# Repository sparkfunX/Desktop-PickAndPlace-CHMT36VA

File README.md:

SparkFun Charm High Desktop Pick and Place
========================================

The CHMT36VA is a $2800 desktop sized pick and place machine from Charm High. We use it to produce a variety of designs, 50 to 100pcs at a shot. It works very well for low-volume high-mix pick and place of 0603 based designs.

The main purposed of this repo is the [Eagle Conversion ULP](https://github.com/sparkfunX/Desktop-PickAndPlace-CHMT36VA/tree/master/Eagle-Conversion) and the English Language file. The Conversion ULP offers the user a GUI that looks like this:

This allows the user to take in an Eagle BRD file and output the recipe file that the CHMT36VA expects. This cuts down on setup time of the machine dramatically.

The [English Language conversion file](https://github.com/sparkfunX/Desktop-PickAndPlace-CHMT36VA/tree/master/Language-File) is our translation and typo fixes of the Charm High provided english file.

Do you have one of these machines? Want to share your tips and tricks and ask other owners a question? Join the [Desktop Pick and Place google group](https://groups.google.com/d/forum/desktop-pick-and-place)!

Be sure to checkout our posts on the machine:

* [Unboxing](https://www.sparkfun.com/sparkx/blog/2586)
* [Leader Cheaters](https://www.sparkfun.com/sparkx/blog/2588)
* [Installing the Charm High Software](https://www.sparkfun.com/sparkx/blog/2594)
* [A better English translation](https://www.sparkfun.com/sparkx/blog/2595)
* [An EAGLE ULP](https://www.sparkfun.com/sparkx/blog/2591) to setup new jobs on the machine quickly

Repository Contents
-------------------

* **/Eagle-Conversion** - Takes an EAGLE design and outputs a work file complete with feeder data. See [SparkFun Charm EAGLE Conversion ULP](https://www.sparkfun.com/sparkx/blog/2591) for more information.
* **/KiCad-Conversion** - Same as EAGLE but less developed. It works, but less bells and whistles.
* **/Language-File** - A new smt_English.qm file for easier to understand error messages and buttons
* **/Software** - The various versions of the Windows based Charm High software
* **/User-Manuals** - Various manuals from different machines in an attempt to piece together various poorly translated or documented features

Related Projects
----------------

* [PNPConvert](https://github.com/hydra/pnpconvert) Conversion utility with DipTrace support, written in Groovy.

License Information
-------------------

This product is _**open source**_! 

Please review the LICENSE.md file for license information. 

If you have any questions or concerns on licensing, please contact techsupport@sparkfun.com.

Please use, reuse, and modify these files as you see fit. Please maintain attribution to SparkFun Electronics and release any derivative under the same license.

Distributed as-is; no warranty is given.

- Your friends at SparkFun.

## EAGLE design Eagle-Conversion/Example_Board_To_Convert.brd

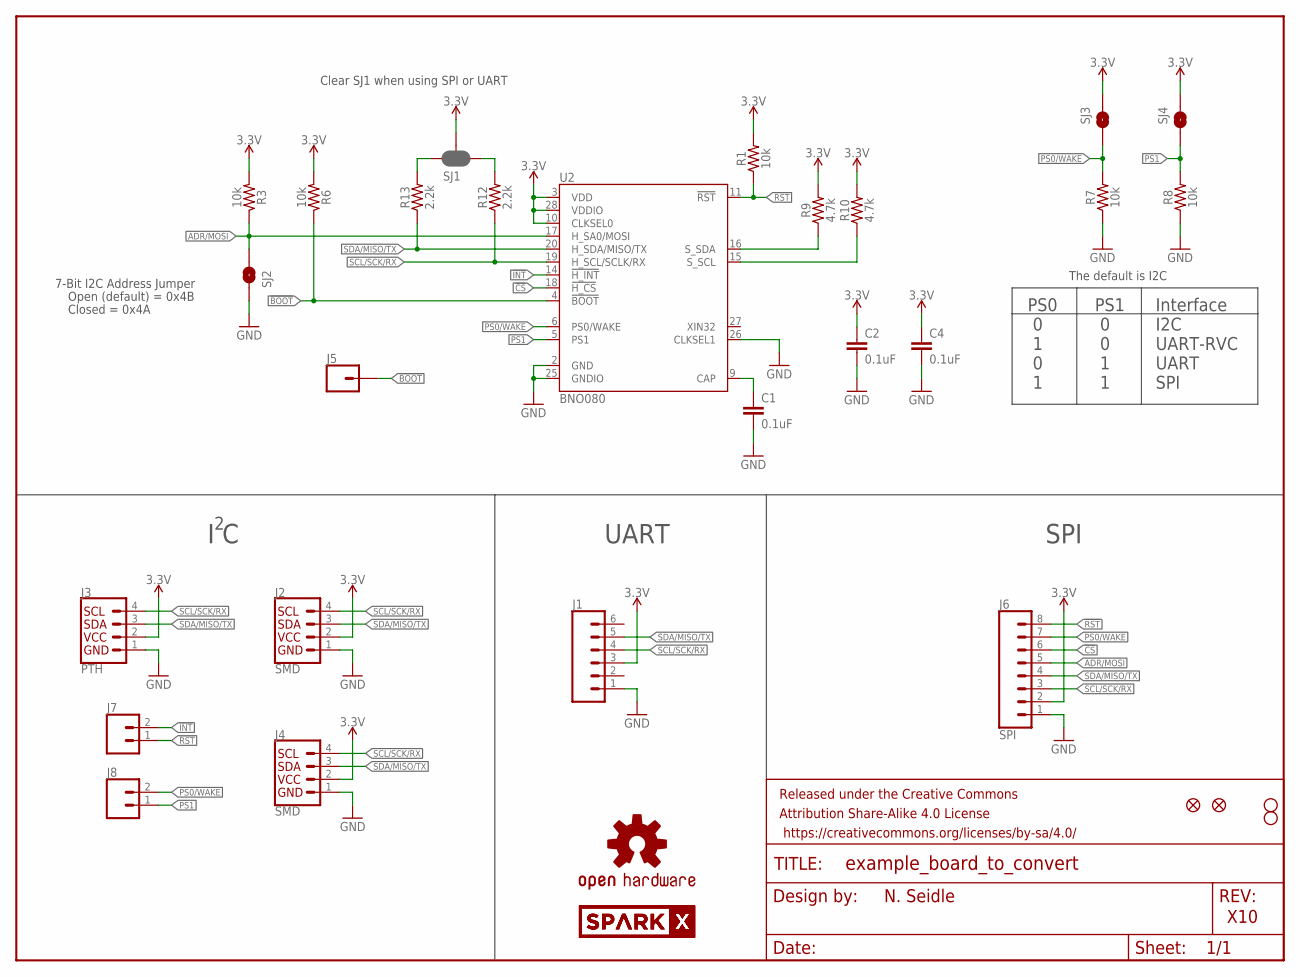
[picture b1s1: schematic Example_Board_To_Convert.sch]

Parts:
C1, C2, C4: 0.1uF; 0603
FRAME1: FRAME-LETTER; CREATIVE_COMMONS
J1: CONN_06NO_SILK_FEMALE_PTH; 1X06_NO_SILK
J2, J4: SMD; 1X04_1MM_RA
J3: PTH; 1X04_NO_SILK
J5: CONN_01PTH_NO_SILK_YES_STOP; 1X01_NO_SILK
J6: SPI; 1X08_NO_SILK
J7, J8: CONN_021X02_NO_SILK; 1X02_NO_SILK
JP2, JP6: FIDUCIALUFIDUCIAL; MICRO-FIDUCIAL
JP3, JP4: STAND-OFF
LOGO1: OSHW-LOGOMINI; OSHW-LOGO-MINI
R1, R3, R6, R7, R8: 10k; 0603
R9, R10: 4.7k; 0603
R12, R13: 2.2k; 0603
SJ1: JUMPER-SMT_3_2-NC_PASTE_SILK; SMT-JUMPER_3_2-NC_PASTE_SILK
SJ2, SJ3, SJ4: SOLDERJUMPERNO; SJ_2S-NO
U2: BNO080; LGA-28
U$1, U$2: SPARKX-LOGO3; SPARKX-SMALL

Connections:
3.3V: C2.1, C4.1, J1.3, J2.2 (VCC), J3.2 (VCC), J4.2 (VCC), J6.2, R1.2, R3.2, R6.2, R9.2, R10.2, SJ1.2, SJ3.1, SJ4.1, U2.3 (VDD), U2.10 (CLKSEL0), U2.28 (VDDIO)
!BOOT: J5.1, R6.1, U2.4 (!BOOT)
!CS: J6.6, U2.18 (!H_CS)
!INT: J7.2, U2.14 (!H_INT)
!RST: J6.8, J7.1, R1.1, U2.11 (!RST)
ADR/MOSI: J6.5, R3.1, SJ2.2, U2.17 (H_SA0/MOSI)
CAP: C1.1, U2.9 (CAP)
GND: C1.2, C2.2, C4.2, J1.1, J2.1 (GND), J3.1 (GND), J4.1 (GND), J6.1, R7.1, R8.1, SJ2.1, U2.2 (GND), U2.25 (GNDIO), U2.26 (CLKSEL1)
PS0/WAKE: J6.7, J8.2, R7.2, SJ3.2, U2.6 (PS0/WAKE)
PS1: J8.1, R8.2, SJ4.2, U2.5 (PS1)
SCL/SCK/RX: J1.4, J2.4 (SCL), J3.4 (SCL), J4.4 (SCL), J6.3, R12.1, U2.19 (H_SCL/SCLK/RX)
SCL_PU: R12.2, SJ1.1
SDA/MISO/TX: J1.5, J2.3 (SDA), J3.3 (SDA), J4.3 (SDA), J6.4, R13.1, U2.20 (H_SDA/MISO/TX)
SDA_PU: R13.2, SJ1.3
S_SCL: R10.1, U2.15 (S_SCL)
S_SDA: R9.1, U2.16 (S_SDA)

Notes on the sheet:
N. Seidle
X10
7-Bit I2C Address Jumper
Closed = 0x4A
Open (default) = 0x4B
PS0 0 1 0 1
PS1 0 0 1 1
Interface I2C UART-RVC UART SPI
The default is I2C
Clear SJ1 when using SPI or UART
I C
UART
SPI

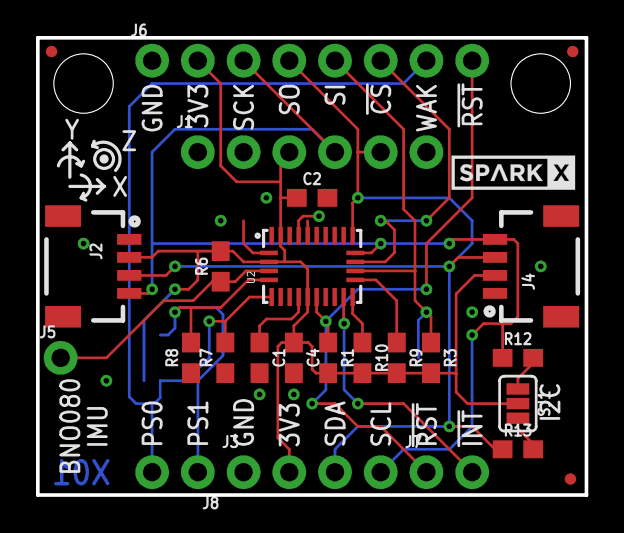
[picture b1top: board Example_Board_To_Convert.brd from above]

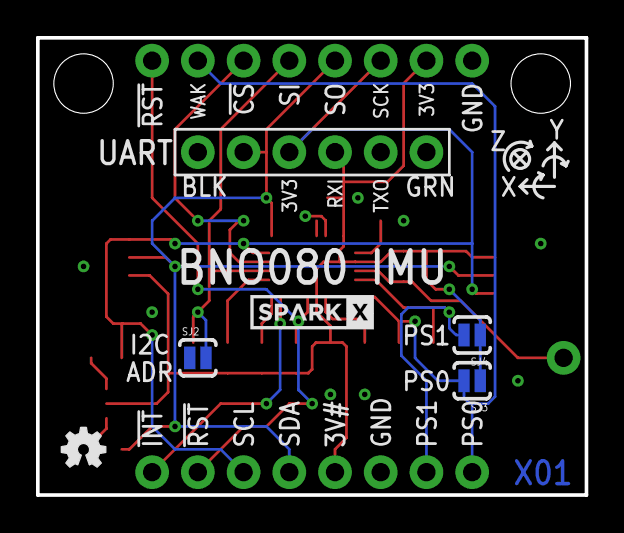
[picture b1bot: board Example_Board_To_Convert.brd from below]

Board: 2 copper layers, 30.5 x 25.4 mm, 34 parts (5 on the bottom side), 16 nets.

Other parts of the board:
JP1: FIDUCIALUFIDUCIAL; MICRO-FIDUCIAL

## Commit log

2018-01-25 Adding credentials shield
2018-01-25 Making credential search work
2018-01-26 Adding KiCad scripts and manuals
2018-01-29 Adding KiCad converter. Adding manuals.
2018-01-29 Adding Qt editor for Windows
2018-01-29 Readme update
2018-02-01 Correcting white space bug.
    If component was not found in feeder data the program would fail. Fix was to only check for component specific data if it was indeed located in the feeder data array.
2018-02-02 Adding readme for kicad gotchas to avoid.
2018-02-08 Work in progress
2018-02-09 Implemented two layer export capabilities and length/width of component
2018-02-09 Major restructuring of the ULP with several new features
    a) Added GUI to review Part Placement and Feeder configuration
    b) Allow usage of local and remote spreadsheet for feeders
    c) Added column autodetection for feeder configuration
    d) Added board statistics
    e) Added automatic offset correction
    -> Only positive coordinates will be in the final file
2018-02-09 Remove offset from KiCad converter
2018-02-09 Adding ignore for credentials
2018-02-09 Revert "Adding readme for kicad gotchas to avoid."
    This reverts commit 1ee665d34516afad8c6f67a0673c987d52c927f7.
2018-02-09 Fixing bad defaults
2018-02-09 Fix issue 6 - relative tape angles now being read
2018-02-09 Fixing issue 7 - centroids now calculated correctly
2018-02-09 Adding toLower() on part names for better matching
2018-02-09 Adding toLower for better feeder ID
2018-02-09 Fixed issue 2 - pulls in human readable comp names
2018-02-10 Fixed issue 3 - adding default file save location
2018-02-12 Several improvements concerning offset handling a) Added possibility to select between automatic and manual offset b) Added warning if negative coordinates are present d) Added preview of placement c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
2018-02-13 Fixed width/height for cameras to detect outlines correctly
2018-02-14 Allows to config trays (and pick-up pockets) to be configured with the ULP
2018-03-05 Offset option is now loaded from file
2018-03-06 Getting NoMount parts from spreadsheet to correctly read. Not yet working.
2018-03-06 getFeederID modified to find partial matches of component name and alias from sheet
2018-03-06 Updated translations for the inner systems menu.
2018-03-20 Fixing 'No Mount' checking from spreadsheet. Adding GUI image.
2018-03-20 Adding GUI image to readme.
2018-03-31 Adding google group to readme
2018-03-31 Adding catch for component angles that are too negative.
2018-03-31 Fix issue 16: Ignore blank lines in feeder spreadsheet.
2018-03-31 Fix issue #15. Tighten comparison of component names to feeder names and aliases. Fix double listings in "Feeders Used" tab.
2018-03-31 Comment and whitespace cleanup
2018-03-31 White space and comment changes
2018-04-08 Adding tips and tricks
2018-04-09 Add internal images, some random hints, updated ticks-n-tips readme
2018-06-25 Fixed some minor issues and added fiducial handling for better pcb calibration
2018-06-25 Fixed some bugs and added possibility to turn of fiducial referencing and added a third mark to Nathans PCB example
2018-07-26 Adding firmware from Rickard. Adds 3rd cal spot and some translation fixes.
2018-08-17 Adding manuals from jmartinis
2018-08-27 Adding editable versions of the improved user manuals and undocumented menus.
2018-10-11 Adding Turkish translation of CHM-T36VA user manual. Thanks Naci!
2018-10-21 Add PCB images
2018-11-21 Started work. In progress
2019-01-15 Adding hardware pinout, ic bom list, and mechanics specs.
2019-03-05 apply change from steve, 02-10-18: py3 mainly
2019-03-05 repr and component_name()
2019-03-05 Fixing awful loop iteration
2019-03-05 bad print messages
2019-03-05 Improve printing infos
2019-03-05 fix print message
2019-03-05 using the spreadsheet key at the begining of the file
2019-03-05 used in design become count in design
2019-03-05 fix for fiducial
2019-03-05 NewSkip cmp are added to the output file as notmounted, for manual add
2019-03-05 args, message and help
2019-03-08 Fix component rotation
2019-03-08 Apply global X/Y correction to NoMount and NewSkip components as well
2019-03-08 Add command line arguments for bottom pos files Rotation and x values have to be mirrored.
2019-03-08 Apply rotation correction to all components, including NoMount and NewSkip
2019-03-08 Keep component value/reference for NewSkip components
2019-04-03 Add link to PnPConvert.
2019-04-17 Support ods/fods/xls/xlsx feeder data files (uses pyexcel instead of builtin csv.reader)
2019-04-18 Set the default output file name using the comp. position file name
2019-04-18 DPV file : include only the filename, not the full path
2019-04-18 Match Eagle script capabilities and output syntax
2019-04-18 Do not include NoMount and add an option for NewSkip components. For NewSkip the feeder ID is set to 99 to avoid triggering an error in the CharmHigh software.
2019-04-18 Auto detect fiducials based on designator
2019-04-18 Add a command line option for a global offset
2019-04-18 KiCad conversion script documentation
2019-04-18 KiCad conversion README typos and clarification
2019-04-29 Compatibility for older py versions
2019-06-09 Add BOM Generator, with automount entry
2019-06-12 Update ConvertToCharm.ulp
    Changed FEEDER_NO_MOUNT from 30 to 999 for requested PR.
2019-06-27 removing unused Reel file
2019-06-27 adding first version, never used in prod
2019-06-27 adding doc
2019-07-11 KiCad conversion: Fix crash when a cut tape row has no alias
2019-07-11 KiCad conversion: strip whitespace from text based columns
2019-10-01 avoid strip on None value
2019-10-01 added Panel settings
2019-10-02 added Panel settings dialogue and explanatory image
2019-10-02 dose no longer ignore Stop-Marks within documents
2019-10-02 is now executable in schematic
2019-10-03 recognises double-sided parts now mostly useful for Fiducials
2019-10-04 dose accept the normal google spreadsheet url now not just the download url
2019-10-15 bug fixes: does no longer have huge coordinates
2019-10-16 Fixed panel offset caluclation and handling to produce correct results
2019-10-16 Fixed google docs URL conversion
2019-10-16 Improvements 1) Added proper panel handling 2) Don't ignore stop record 3) Allow double sided fiducials 4) Always pick the outermost fiducials 5) Google Docs URLs can now be pasted directly
2020-02-17 Files opened in UTF-8
    Files are opened using UTF-8.
    UTF-8 allows to name components using "μ" or "Ω" instead of "u" or "ohm".
2020-02-18 Added clear_utf8_characters function
    This function search for greek letters or "μ" or "Ω" and it substitutes them for "u" and "Ohm".
2020-02-19 bom_file gen includes unassigned comp if set
2020-02-19 improve msg and bom files
2020-02-19 Added UTF-8 support for Cut Tape Configurations
    Yesterday I didn't added it, now when I was using the script I was using cut tape and I realized the mistake and I amended it.
2020-02-21 Add camera calibration proceedure.
2020-02-29 first version of a setup.py
2020-07-30 Feeder component height was not being respected. Added one line to fix
2020-07-30 Removed blank line. Still fixed height
2020-10-28 update commit firmware and software

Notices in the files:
parts and their libraries:
SparkFun-Resistors: Licensing: Creative Commons ShareAlike 4.0 International - https://creativecommons.org/licenses/by-sa/4.0
SparkFun-Aesthetics: Released under the Creative Commons Attribution Share-Alike 4.0 License
SparkFun-Aesthetics: https://creativecommons.org/licenses/by-sa/4.0
